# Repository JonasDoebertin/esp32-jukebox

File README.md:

# Jukebox

An ESP32 based jukebox driven by ESPHome and Home Assistant.

---

About the project: it’s a simple ESP32 based media player that allows scanning cards with RFID tags to select the media to play. Everything will be tight together with ESPHome (for the ESP32 firmware side) and Home Assistant.

It’s a simple 2-layer board with 1.6mm thickness and 4cm x 6cm overall size.

The board features the following main parts:

- ESP32-WROOM-32E as the MCU
- AMS1117-3.3 as a power regulator
- CH340C as the serial converter
- MAX98357AETE+T as a DAC with integrated 3w amp
- connectors for three simple buttons (volume -/+, play/pause)
- connector for an PN532 based RFID module connected via I2C
- connector for a passive broadband speaker

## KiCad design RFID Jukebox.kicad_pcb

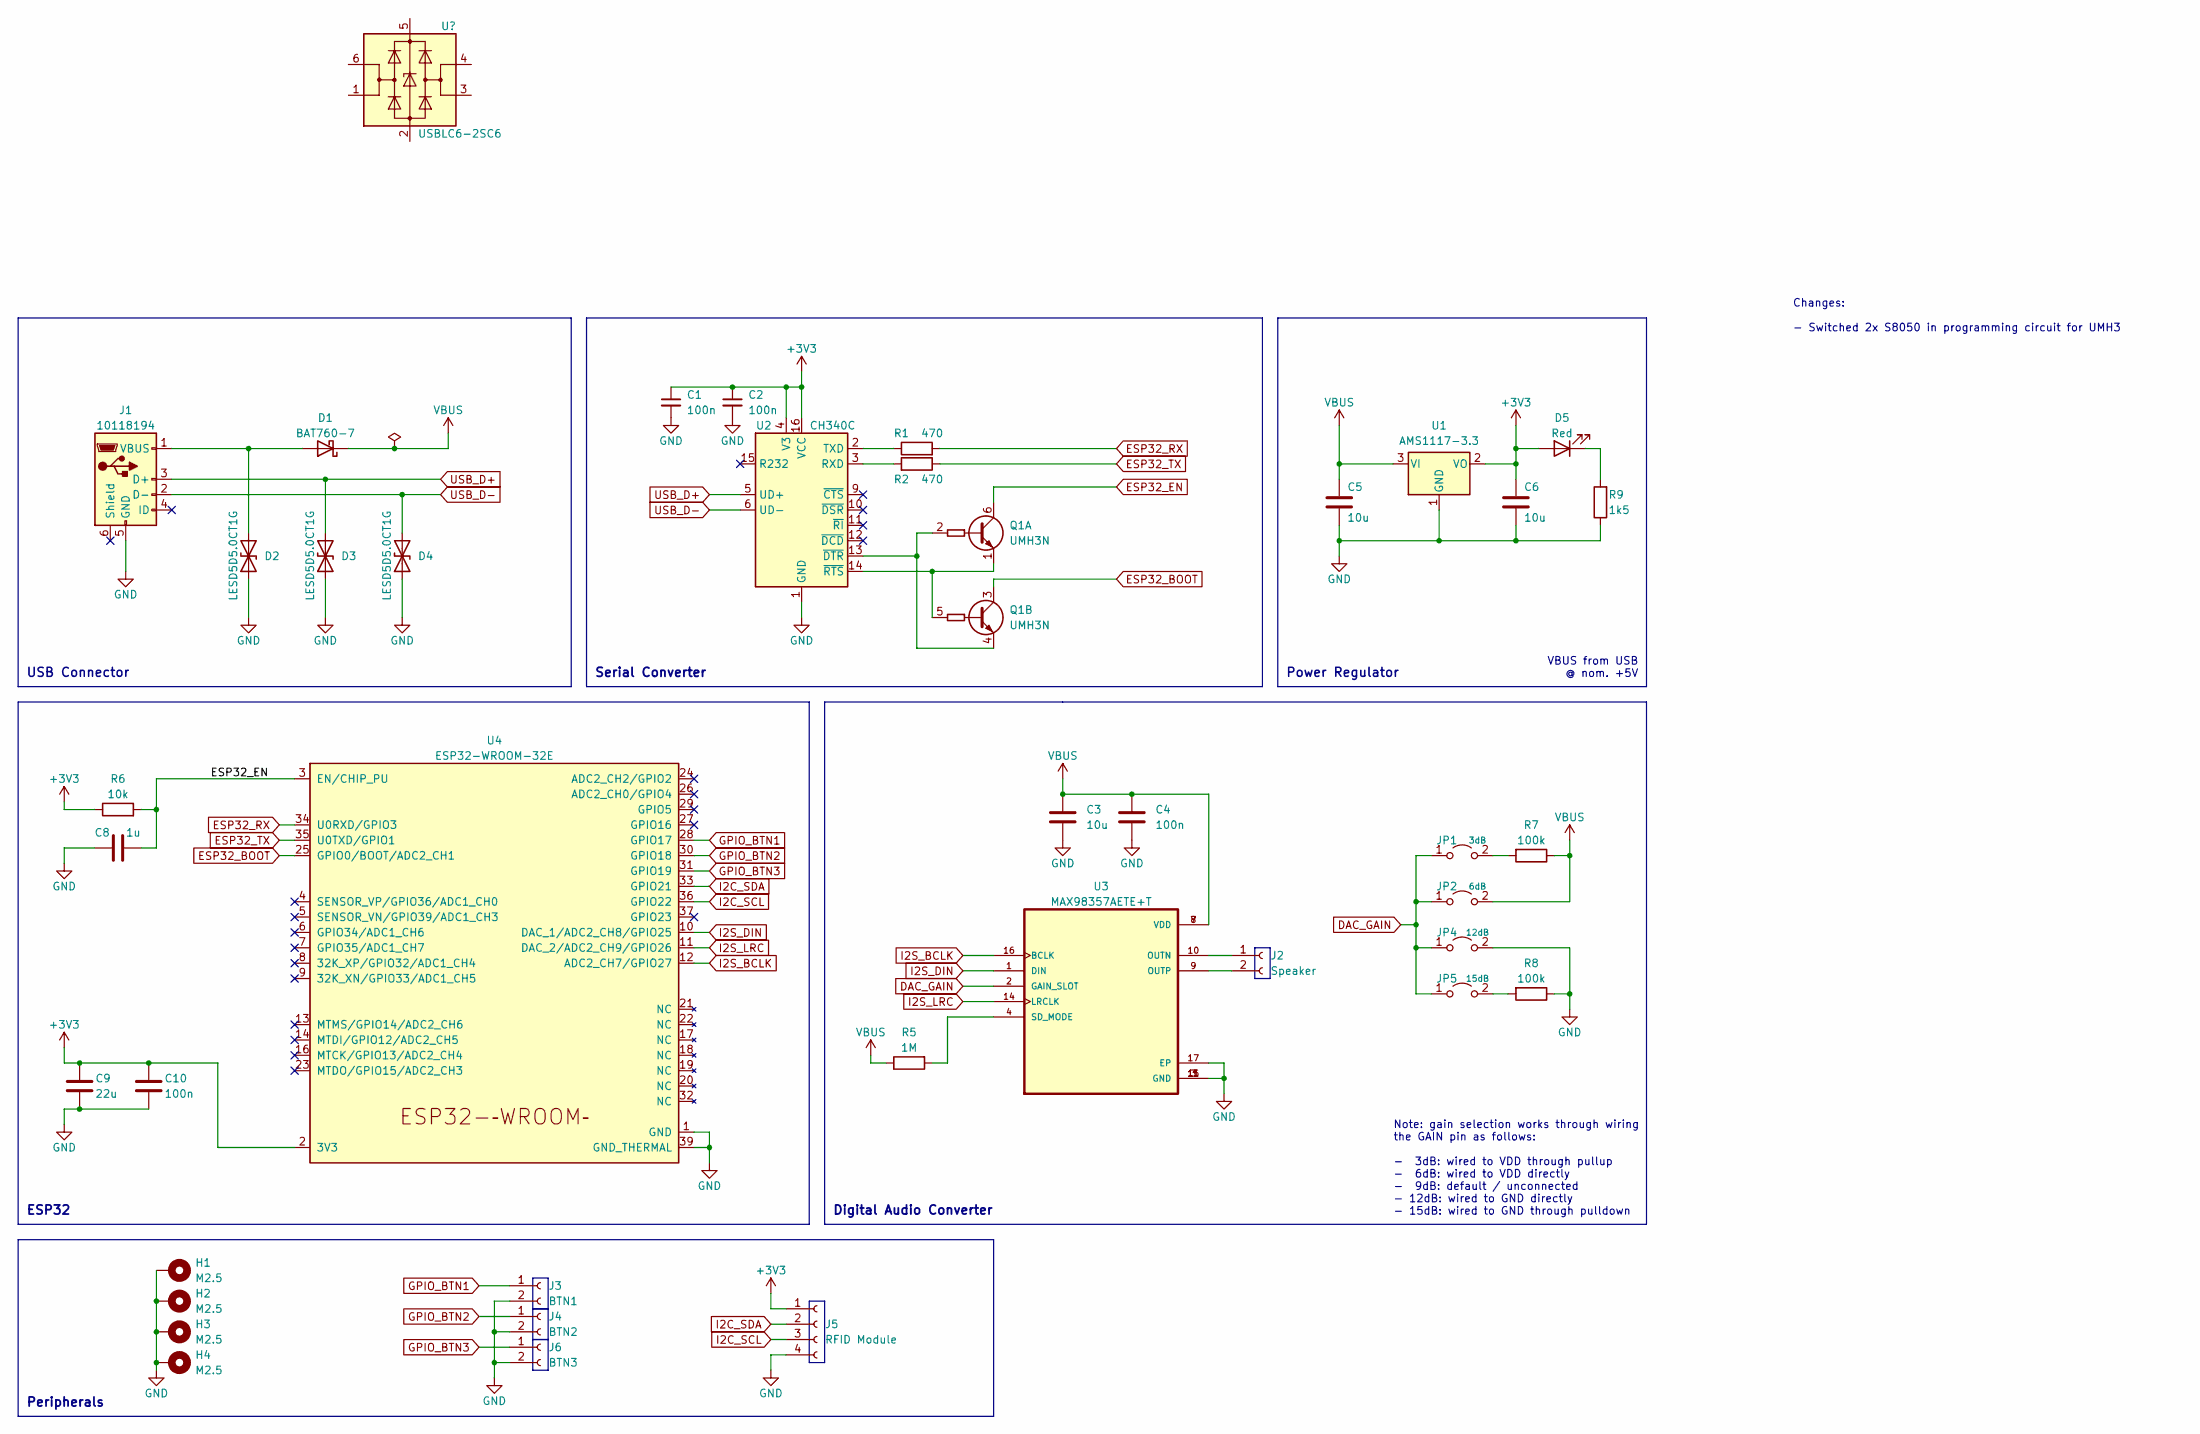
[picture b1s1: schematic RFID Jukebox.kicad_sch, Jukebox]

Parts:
C1, C2, C4, C10: 100n; C_0603_1608Metric; LCSC C14663
C3: 10u; C_0603_1608Metric; LCSC C96446
C5, C6: 10u; C_0805_2012Metric; LCSC C15850
C8: 1u; C_0603_1608Metric; LCSC C15849
C9: 22u; C_0805_2012Metric; LCSC C45783
D1: BAT760-7; D_SOD-323; LCSC C124187
D2, D3, D4: LESD5D5.0CT1G; D_SOD-523; LCSC C383211
D5: Red; LED_0603_1608Metric; LCSC C2286
H1, H2, H3, H4: M2.5; MountingHole_2.7mm_M2.5_Pad_Via
J1: 10118194; USB_Micro-B_Amphenol_10118194_Horizontal; LCSC C132563
J2: Speaker; Molex_KK-254_AE-6410-02A_1x02_P2.54mm_Vertical
J3: BTN1; Molex_KK-254_AE-6410-02A_1x02_P2.54mm_Vertical
J4: BTN2; Molex_KK-254_AE-6410-02A_1x02_P2.54mm_Vertical
J5: RFID Module; Molex_KK-254_AE-6410-04A_1x04_P2.54mm_Vertical
J6: BTN3; Molex_KK-254_AE-6410-02A_1x02_P2.54mm_Vertical
JP1: 3dB; PinHeader_1x02_P2.54mm_Vertical
JP2: 6dB; PinHeader_1x02_P2.54mm_Vertical
JP4: 12dB; PinHeader_1x02_P2.54mm_Vertical
JP5: 15dB; PinHeader_1x02_P2.54mm_Vertical
Q1: UMH3N; SOT-363_SC-70-6; LCSC C62892
R1, R2: 470; R_0603_1608Metric; LCSC C23179
R5: 1M; R_0805_2012Metric; LCSC C17514
R6: 10k; R_0603_1608Metric; LCSC C25804
R7, R8: 100k; R_0603_1608Metric; LCSC C25803
R9: 1k5; R_0603_1608Metric; LCSC C22843
U1: AMS1117-3.3; SOT-223-3_TabPin2; LCSC C6186
U2: CH340C; SOIC-16_3.9x9.9mm_P1.27mm; LCSC C84681
U3: MAX98357AETE+T; TQFN-16-1EP_3x3mm_P0.5mm_EP1.23x1.23mm; LCSC C910544
U4: ESP32-WROOM-32E; LCSC C701341

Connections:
+3V3: C1.1, C2.1, C6.1, C9.1, C10.1, D5.2 (A), J5.1, R6.1, U1.2 (VO), U2.4 (V3), U2.16 (VCC), U4.2 (3V3)
DAC_GAIN: JP1.1 (A), JP2.1 (A), JP4.1 (A), JP5.1 (A), U3.2 (GAIN_SLOT)
ESP32_BOOT: Q1.3 (C2), U4.25 (GPIO0/BOOT/ADC2_CH1)
ESP32_EN: C8.2, Q1.6 (C1), R6.2, U4.3 (EN/CHIP_PU)
ESP32_RX: R1.2, U4.34 (U0RXD/GPIO3)
ESP32_TX: R2.1, U4.35 (U0TXD/GPIO1)
GND: C1.2, C2.2, C3.2, C4.2, C5.2, C6.2, C8.1, C9.2, C10.2, D2.1 (A1), D3.1 (A1), D4.1 (A1), H1.1, H2.1, H3.1, H4.1, J1.5 (GND), J3.2, J4.2, J5.4, J6.2, JP4.2 (B), R8.1, R9.1, U1.1 (GND), U2.1 (GND), U3.3 (GND), U3.11 (GND), U3.15 (GND), U3.17 (EP), U4.1 (GND), U4.15 (GND), U4.38 (GND), U4.39 (GND_THERMAL)
GPIO_BTN1: J3.1, U4.28 (GPIO17)
GPIO_BTN2: J4.1, U4.30 (GPIO18)
GPIO_BTN3: J6.1, U4.31 (GPIO19)
I2C_SCL: J5.3, U4.36 (GPIO22)
I2C_SDA: J5.2, U4.33 (GPIO21)
I2S_BCLK: U3.16 (BCLK), U4.12 (ADC2_CH7/GPIO27)
I2S_DIN: U3.1 (DIN), U4.10 (DAC_1/ADC2_CH8/GPIO25)
I2S_LRC: U3.14 (LRCLK), U4.11 (DAC_2/ADC2_CH9/GPIO26)
unnamed: D1.2 (A), D2.2 (A2), J1.1 (VBUS)
unnamed: D5.1 (K), R9.2
unnamed: J2.1, U3.10 (OUTN)
unnamed: J2.2, U3.9 (OUTP)
unnamed: JP1.2 (B), R7.2
unnamed: JP5.2 (B), R8.2
unnamed: Q1.1 (E1), Q1.5 (B2), U2.14 (~RTS)
unnamed: Q1.2 (B1), Q1.4 (E2), U2.13 (~DTR)
unnamed: R1.1, U2.2 (TXD)
unnamed: R2.2, U2.3 (RXD)
unnamed: R5.2, U3.4 (SD_MODE)
USB_D+: D3.2 (A2), J1.3 (D+), U2.5 (UD+)
USB_D-: D4.2 (A2), J1.2 (D-), U2.6 (UD-)
VBUS: C3.1, C4.1, C5.1, D1.1 (K), JP2.2 (B), R5.1, R7.1, U1.3 (VI), U3.7 (VDD), U3.8 (VDD)

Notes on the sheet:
Digital Audio Converter
Note: gain selection works through wiring the GAIN pin as follows: - 3dB: wired to VDD through pullup - 6dB: wired to VDD directly - 9dB: default / unconnected - 12dB: wired to GND directly - 15dB: wired to GND through pulldown
ESP32
USB Connector
VBUS from USB @ nom. +5V
Changes: - Switched 2x S8050 in programming circuit for UMH3
Power Regulator
Serial Converter
Peripherals

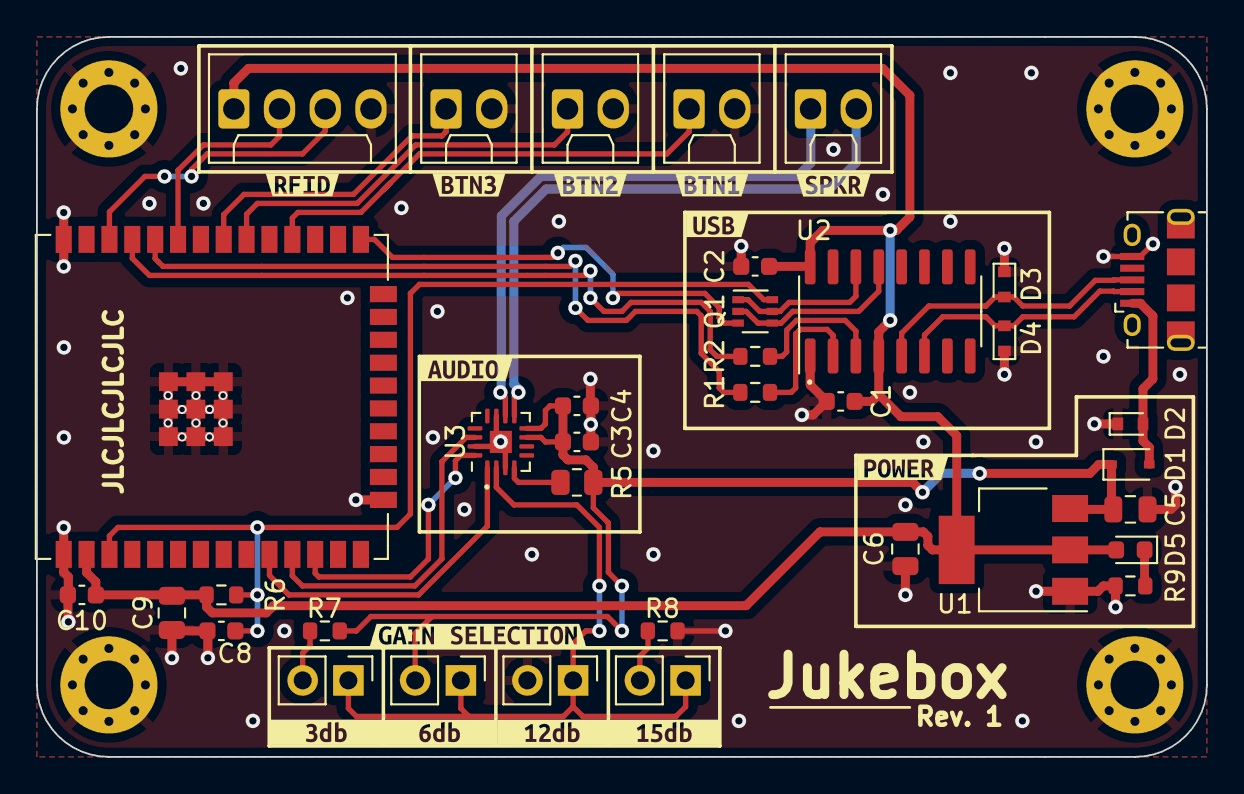
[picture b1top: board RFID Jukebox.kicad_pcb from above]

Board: 2 copper layers, 65.0 x 40.0 mm, 53 parts (0 on the bottom side), 29 nets.

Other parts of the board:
kibuzzard-6380B75E: G***; kibuzzard-6380B75E
kibuzzard-63885EFC: G***; kibuzzard-63885EFC
kibuzzard-63886C2C: G***; kibuzzard-63886C2C
kibuzzard-63886C6D: G***; kibuzzard-63886C6D
kibuzzard-63886C09: G***; kibuzzard-63886C09
kibuzzard-63886C18: G***; kibuzzard-63886C18
kibuzzard-63886C48: G***; kibuzzard-63886C48
kibuzzard-63886C53: G***; kibuzzard-63886C53
kibuzzard-63886C64: G***; kibuzzard-63886C64
kibuzzard-63886C79: G***; kibuzzard-63886C79
kibuzzard-6387301B: G***; kibuzzard-6387301B
kibuzzard-63873011: G***; kibuzzard-63873011
kibuzzard-63873069: G***; kibuzzard-63873069

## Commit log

2022-12-02 add readme
